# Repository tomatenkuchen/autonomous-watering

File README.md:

# autonomous-watering
esp32c6 based, solar powered, battery backuped garden water supply system

## todo
The objective of this project is to have an autonomous-as-can-be field water management system. it supports:
- [ ] multiple 24Vdc water valve connections for water distribution
- [ ] solar power supply to avoid grid wiring
- [ ] battery backup for valve power supply in case no sun is shining. watering is done best after heavy sun hours anyway
- [ ] wifi access point for watering configurations and updates
- [ ] optional conductivity sensor to measure earth humidity
- [ ] maybe maybe wifi powered wether data access to avoid watering just before the storm. GPS data relevant?
- [ ] bonus project: support for an electric fence to have sheep stay away from my salad

## Hardware

can be found in [this](./hw) folder. it's a [kicad](https://www.kicad.org) project, so no worries about licenses.
for now i plan to have an [ESP32C6] as the computing base.

## Software

is found in [this](./sw) folder. as it is an embedded project, it fits the hardware described in the [hardware folder](./hw).

## License

i intent to have the software and hardware licensed for GNU GPLv2. You will find either hardware part libraries or software libraries
licensed under different licenses (duh!), so please check the individual folders and references.

## Liabilities

this is my personal DIY project. It's supposed to be battery backed, so at least no grilling yourself on the grid issues to expected here.
nontheless, electrical danger lurks everywhere. Consider yourself to be warned! If you hurt yourself by soldering stuff, (mis-)handling batteries,
tripping over wires or get struck by lightning while setting up the system outside, blame yourself, not me.

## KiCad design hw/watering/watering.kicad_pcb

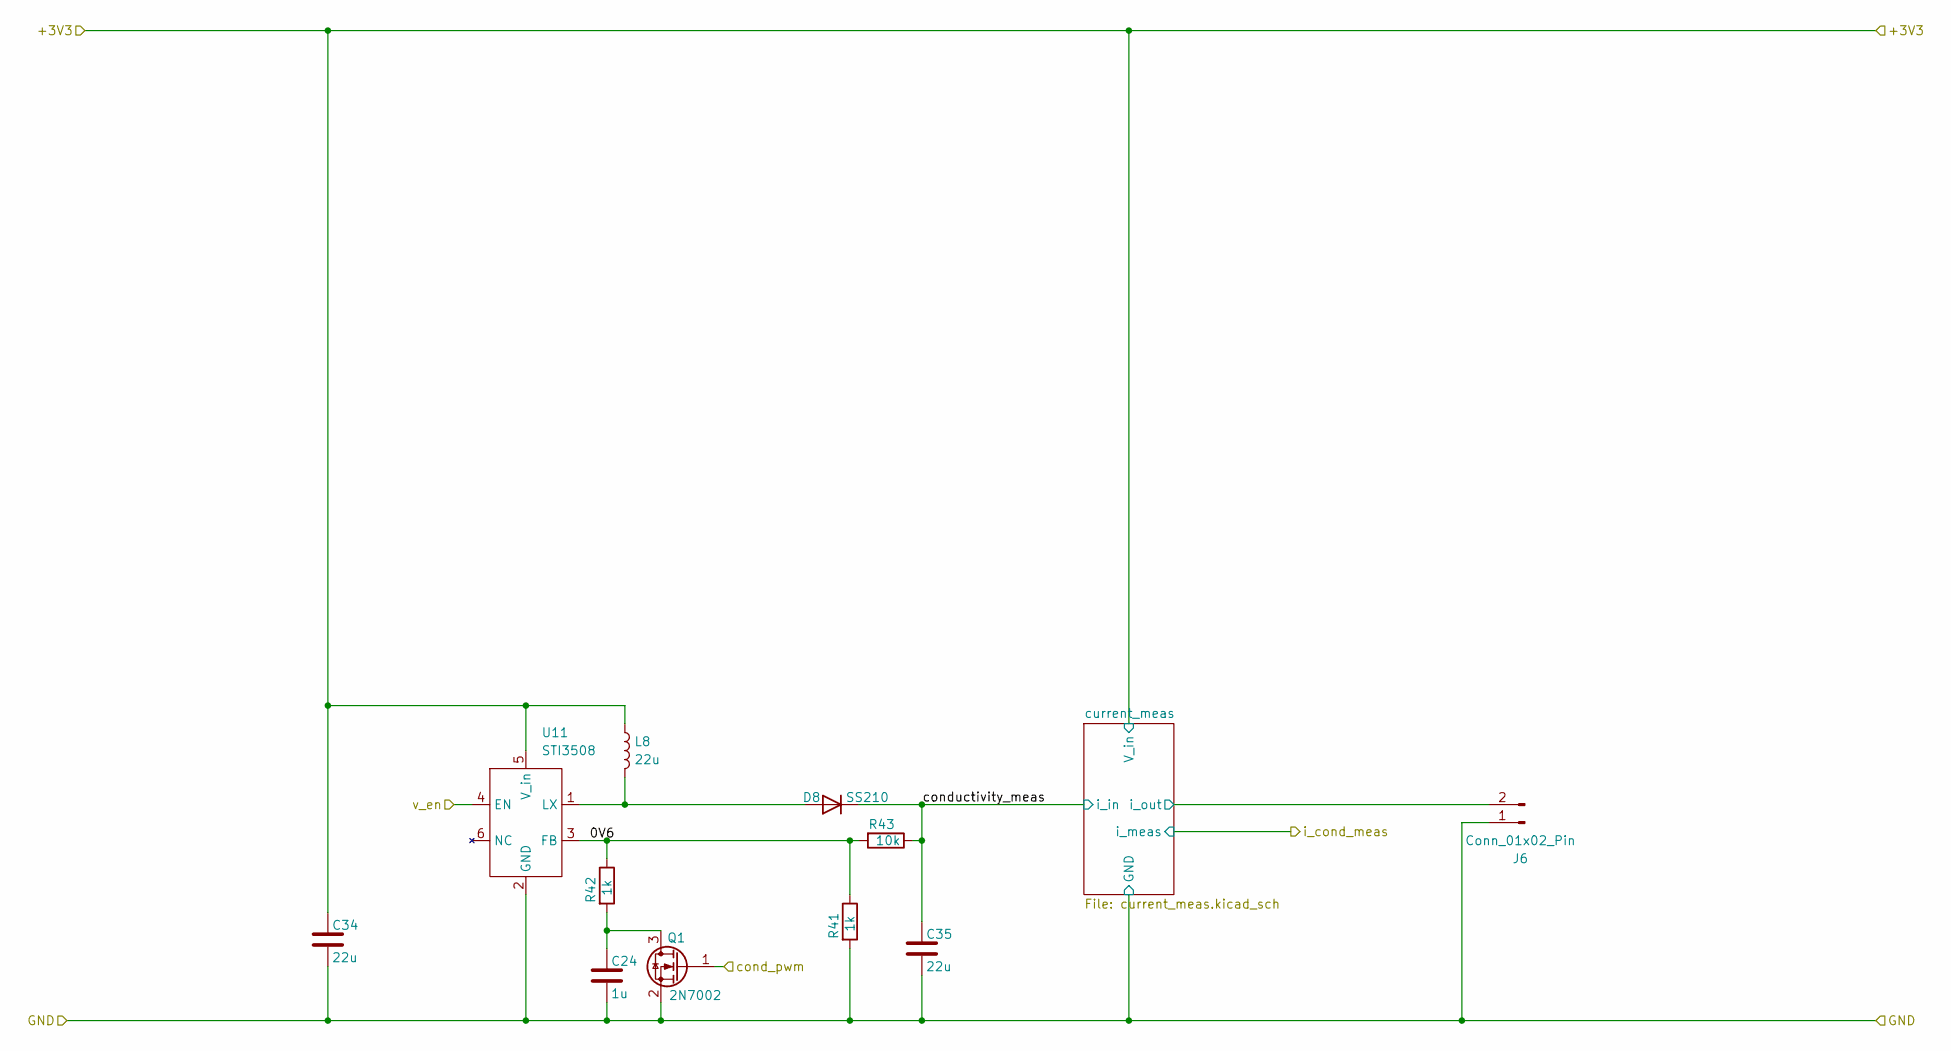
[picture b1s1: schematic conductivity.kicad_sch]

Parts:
C24: 1u; C_0603_1608Metric
C34, C35: 22u; C_1206_3216Metric
D8: SS210; D_SMA
J6: Conn_01x02_Pin; DB142R-5.08-2P-GN
L8: 22u; L_Changjiang_FTC303020D
Q1: 2N7002; SOT-23
R41, R42: 1k; R_0603_1608Metric
R43: 10k; R_0603_1608Metric
U11: STI3508; SOT-23-6

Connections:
/GND: C24.2, C34.2, C35.2, J6.1, Q1.2 (S), R41.2, U11.2 (GND); also elsewhere on the board
/V_bat: C34.1, L8.1, U11.5 (V_in); also elsewhere on the board
/conductivity/0V6: R41.1, R42.1, R43.2, U11.3 (FB)
/conductivity/cond_pwm: Q1.1 (G); also elsewhere on the board
/conductivity/conductivity_meas: C35.1, D8.1 (K), R43.1; also elsewhere on the board
/conductivity/current_meas/i_out: J6.2; also elsewhere on the board
/conductivity/v_en: U11.4 (EN); also elsewhere on the board
unnamed: D8.2 (A), L8.2, U11.1 (LX)
unnamed: C24.1, Q1.3 (D), R42.2

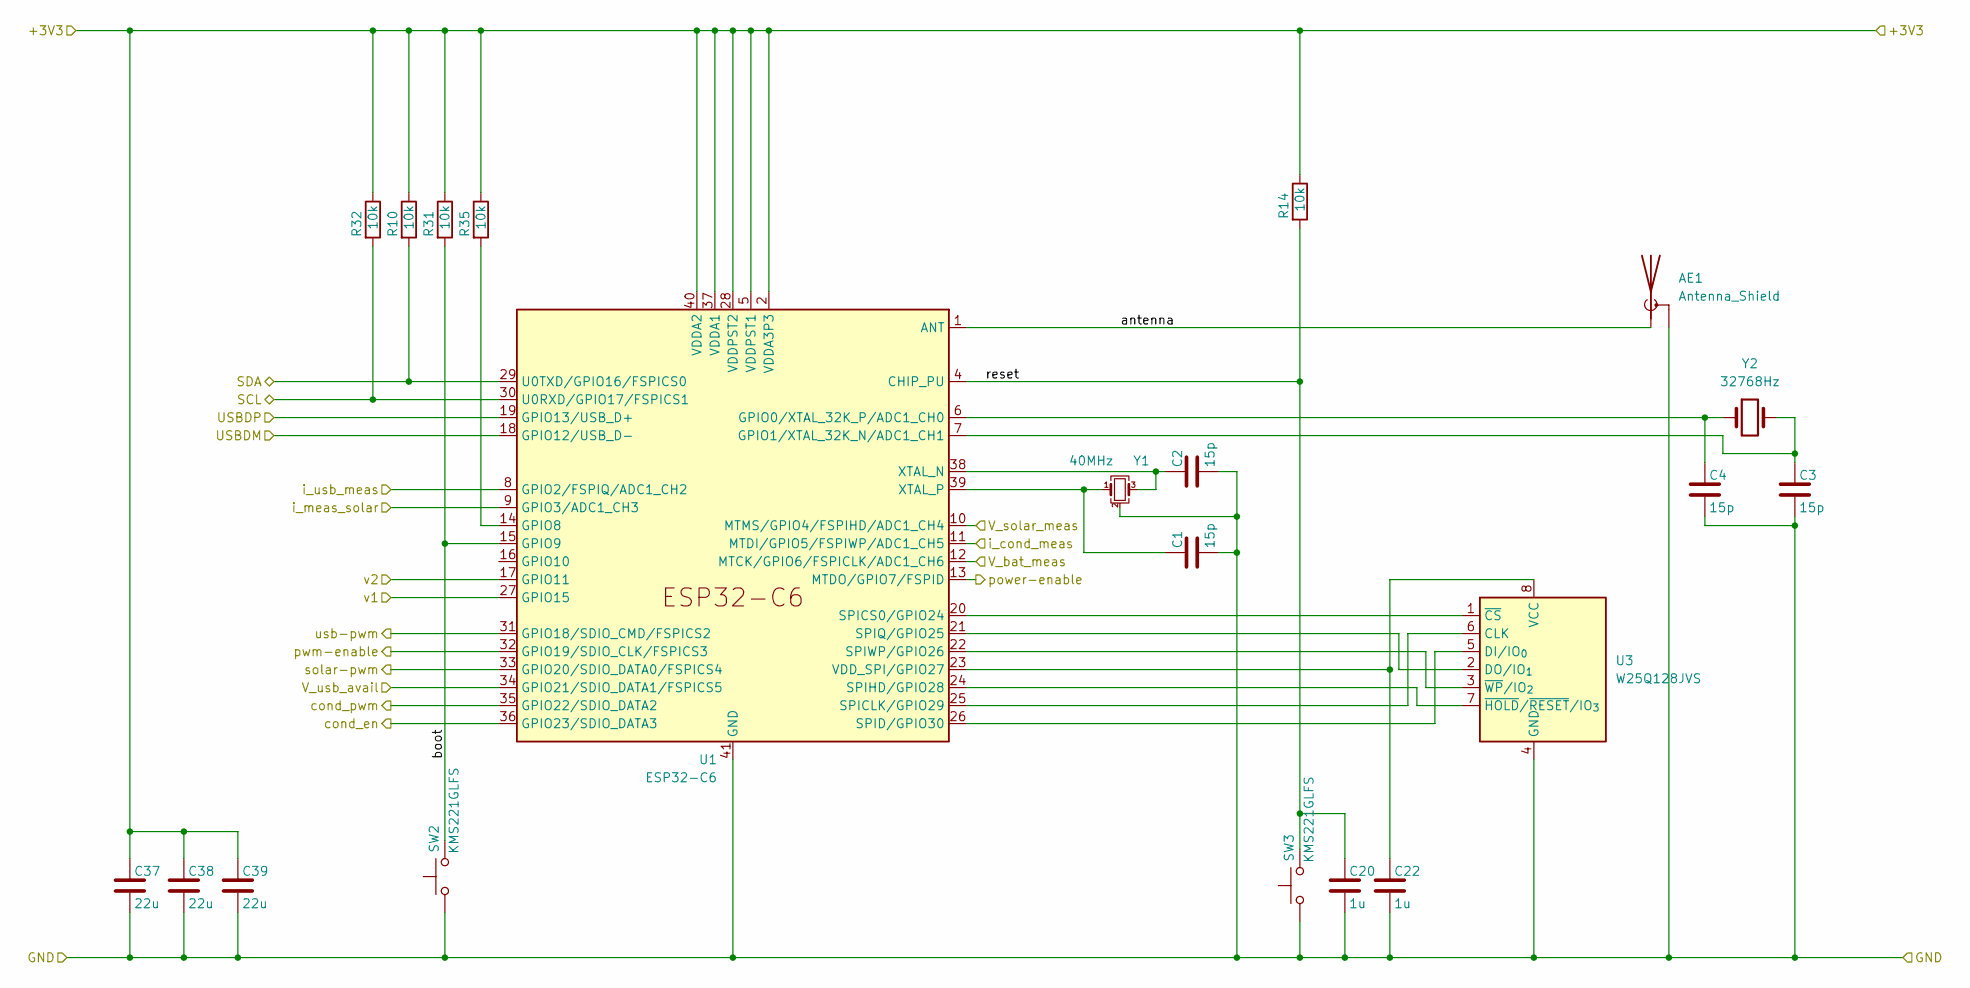
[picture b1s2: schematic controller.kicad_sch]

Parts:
AE1: Antenna_Shield; Texas_SWRA117D_2.4GHz_Left
C1, C2, C3, C4: 15p; C_0603_1608Metric
C20, C22: 1u; C_0603_1608Metric
C37, C38, C39: 22u; C_1206_3216Metric
R10, R14, R31, R32, R35: 10k; R_0603_1608Metric
SW2, SW3: KMS221GLFS; SW_SPST_TS-1088-xR020
U1: ESP32-C6; QFN-40-1EP_5x5mm_P0.4mm_EP3.6x3.6mm
U3: W25Q128JVS; SOIC-8_5.3x5.3mm_P1.27mm
Y1: 40MHz; Crystal_SMD_3225-4Pin_3.2x2.5mm
Y2: 32768Hz; Crystal_SMD_3215-2Pin_3.2x1.5mm

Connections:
/+3V3: C37.1, C38.1, C39.1, R10.1, R14.1, R31.1, R32.1, R35.1, U1.2 (VDDA3P3), U1.3 (VDDA3P3), U1.5 (VDDPST1), U1.28 (VDDPST2), U1.37 (VDDA1), U1.40 (VDDA2); also elsewhere on the board
/GND: AE1.2 (Shield), C1.2, C2.2, C3.2, C4.2, C20.2, C22.2, C37.2, C38.2, C39.2, SW2.1, SW3.1, U1.41 (GND), U3.4 (GND), Y1.2 (G), Y1.4 (G); also elsewhere on the board
/conductivity/cond_pwm: U1.35 (GPIO22/SDIO_DATA2); also elsewhere on the board
/conductivity/i_cond_meas: U1.11 (MTDI/GPIO5/FSPIWP/ADC1_CH5); also elsewhere on the board
/conductivity/v_en: U1.36 (GPIO23/SDIO_DATA3); also elsewhere on the board
/controller/SCL: R32.2, U1.30 (U0RXD/GPIO17/FSPICS1)
/controller/SDA: R10.2, U1.29 (U0TXD/GPIO16/FSPICS0)
/controller/USBDM: U1.18 (GPIO12/USB_D-); also elsewhere on the board
/controller/USBDP: U1.19 (GPIO13/USB_D+); also elsewhere on the board
/controller/V_bat_meas: U1.12 (MTCK/GPIO6/FSPICLK/ADC1_CH6); also elsewhere on the board
/controller/V_solar_meas: U1.10 (MTMS/GPIO4/FSPIHD/ADC1_CH4); also elsewhere on the board
/controller/V_usb_avail: U1.34 (GPIO21/SDIO_DATA1/FSPICS5); also elsewhere on the board
/controller/antenna: AE1.1 (A), U1.1 (ANT)
/controller/boot: R31.2, SW2.2, U1.15 (GPIO9)
/controller/i_meas_solar: U1.9 (GPIO3/ADC1_CH3); also elsewhere on the board
/controller/i_usb_meas: U1.8 (GPIO2/FSPIQ/ADC1_CH2); also elsewhere on the board
/controller/power-enable: U1.13 (MTDO/GPIO7/FSPID)
/controller/pwm-enable: U1.32 (GPIO19/SDIO_CLK/FSPICS3); also elsewhere on the board
/controller/reset: C20.1, R14.2, SW3.2, U1.4 (CHIP_PU)
/controller/solar-pwm: U1.33 (GPIO20/SDIO_DATA0/FSPICS4); also elsewhere on the board
/controller/usb-pwm: U1.31 (GPIO18/SDIO_CMD/FSPICS2); also elsewhere on the board
/controller/v1: U1.27 (GPIO15); also elsewhere on the board
/controller/v2: U1.17 (GPIO11); also elsewhere on the board
unnamed: C4.1, U1.6 (GPIO0/XTAL_32K_P/ADC1_CH0), Y2.1
unnamed: C3.1, U1.7 (GPIO1/XTAL_32K_N/ADC1_CH1), Y2.2
unnamed: R35.2, U1.14 (GPIO8)
unnamed: U1.25 (SPICLK/GPIO29), U3.6 (CLK)
unnamed: U1.20 (SPICS0/GPIO24), U3.1 (~CS)
unnamed: U1.26 (SPID/GPIO30), U3.5 (DI/IO_{0})
unnamed: U1.24 (SPIHD/GPIO28), U3.7 (~HOLD/~RESET/IO_{3})
unnamed: U1.21 (SPIQ/GPIO25), U3.2 (DO/IO_{1})
unnamed: U1.22 (SPIWP/GPIO26), U3.3 (~WP/IO_{2})
unnamed: C22.1, U1.23 (VDD_SPI/GPIO27), U3.8 (VCC)
unnamed: C2.1, U1.38 (XTAL_N), Y1.3
unnamed: C1.1, U1.39 (XTAL_P), Y1.1

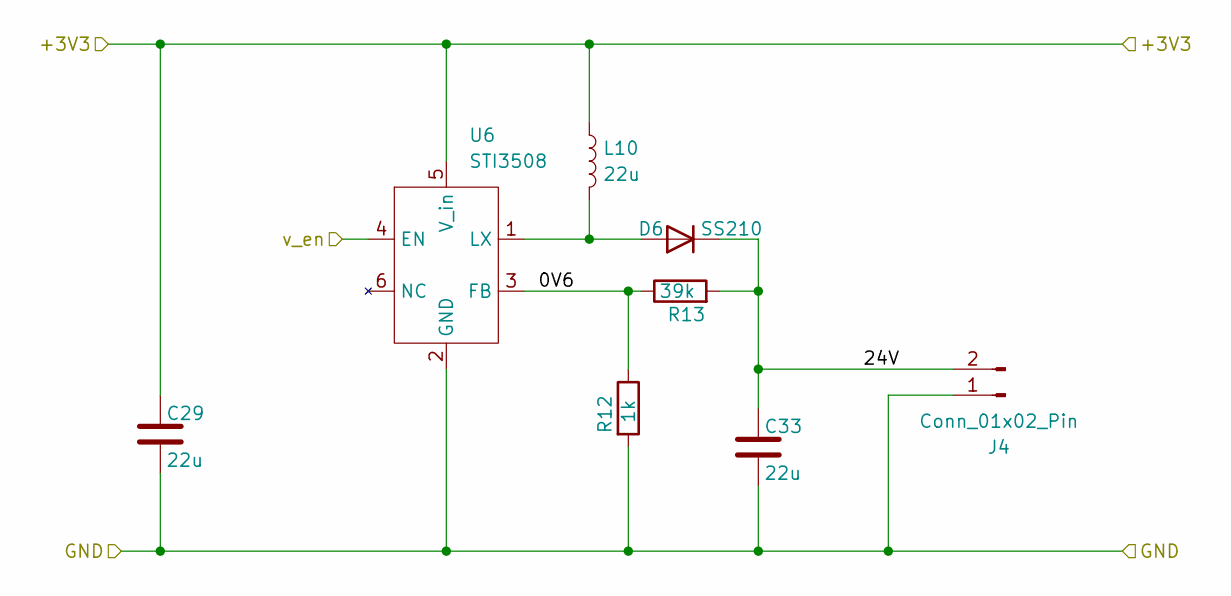
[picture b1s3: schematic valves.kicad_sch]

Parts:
C29, C33: 22u; C_1206_3216Metric
D6: SS210; D_SMA
J4: Conn_01x02_Pin; DB142R-5.08-2P-GN
L10: 22u; L_Changjiang_FTC303020D
R12: 1k; R_0603_1608Metric
R13: 39k; R_0603_1608Metric
U6: STI3508; SOT-23-6

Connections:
/GND: C29.2, C33.2, J4.1, R12.2, U6.2 (GND); also elsewhere on the board
/V_bat: C29.1, L10.1, U6.5 (V_in); also elsewhere on the board
/controller/v2: U6.4 (EN); also elsewhere on the board
/valves2/0V6: R12.1, R13.1, U6.3 (FB)
/valves2/24V: C33.1, D6.1 (K), J4.2, R13.2
unnamed: D6.2 (A), L10.2, U6.1 (LX)

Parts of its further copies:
C28, C30: 22u; C_1206_3216Metric
D7: SS210; D_SMA
J3: Conn_01x02_Pin; DB142R-5.08-2P-GN
L11: 22u; L_Changjiang_FTC303020D
R5: 1k; R_0603_1608Metric
R6: 39k; R_0603_1608Metric
U4: STI3508; SOT-23-6

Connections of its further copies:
/GND: C28.2, C30.2, J3.1, R5.2, U4.2 (GND); also elsewhere on the board
/V_bat: C28.1, L11.1, U4.5 (V_in); also elsewhere on the board
/controller/v1: U4.4 (EN); also elsewhere on the board
/valves1/0V6: R5.1, R6.1, U4.3 (FB)
/valves1/24V: C30.1, D7.1 (K), J3.2, R6.2
unnamed: D7.2 (A), L11.2, U4.1 (LX)

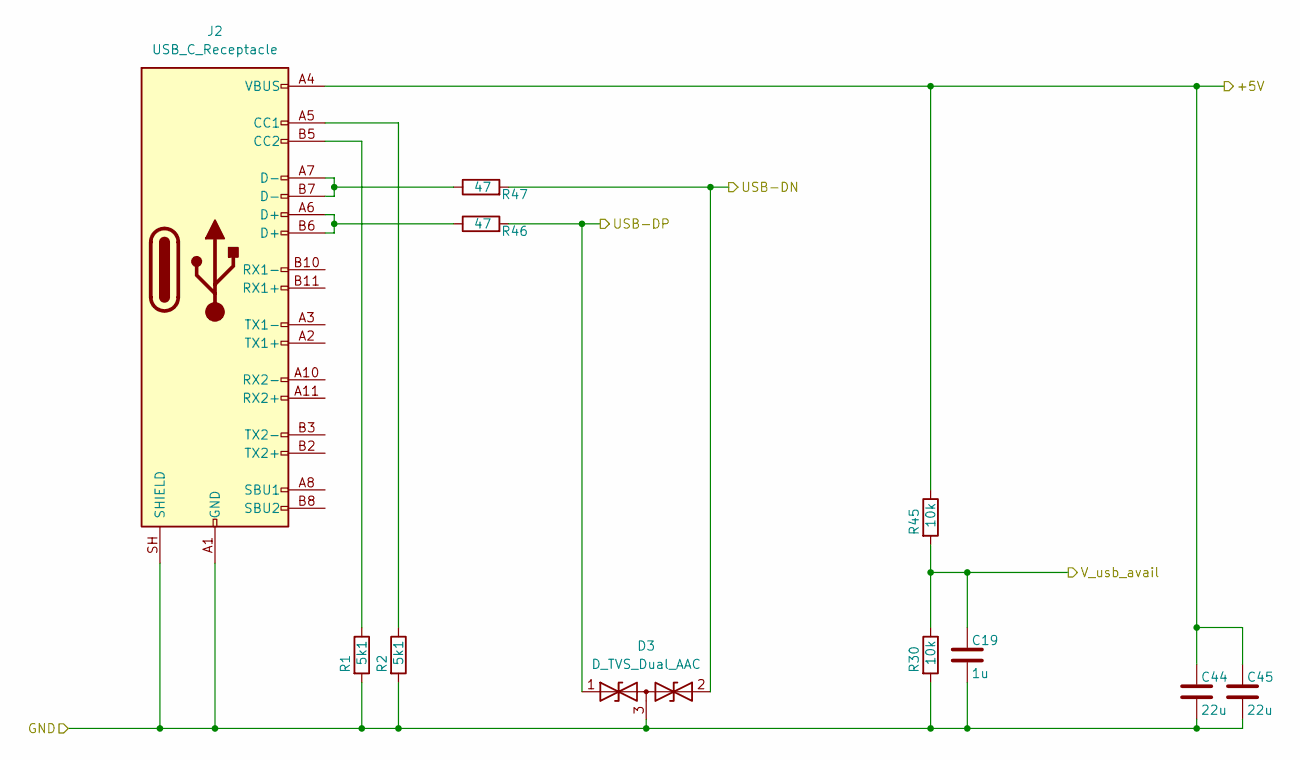
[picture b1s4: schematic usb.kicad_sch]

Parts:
C19: 1u; C_0603_1608Metric
C44, C45: 22u; C_1206_3216Metric
D3: D_TVS_Dual_AAC; TSOT-23
J2: USB_C_Receptacle; USB_C_Receptacle_GCT_USB4105-xx-A_16P_TopMnt_Horizontal
R1, R2: 5k1; R_0603_1608Metric
R30, R45: 10k; R_0603_1608Metric
R46, R47: 47; R_0603_1608Metric

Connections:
/+5V: C44.1, C45.1, J2.A4 (VBUS), J2.A9 (VBUS), J2.B4 (VBUS), J2.B9 (VBUS), R45.1; also elsewhere on the board
/GND: C19.2, C44.2, C45.2, D3.3 (common), J2.A1 (GND), J2.A12 (GND), J2.B1 (GND), J2.B12 (GND), J2.SH (SHIELD), R1.2, R2.2, R30.2; also elsewhere on the board
/controller/USBDM: D3.2 (A2), R47.2; also elsewhere on the board
/controller/USBDP: D3.1 (A1), R46.2; also elsewhere on the board
/controller/V_usb_avail: C19.1, R30.1, R45.2; also elsewhere on the board
unnamed: J2.A5 (CC1), R2.1
unnamed: J2.B5 (CC2), R1.1
unnamed: J2.A6 (D+), J2.B6 (D+), R46.1
unnamed: J2.A7 (D-), J2.B7 (D-), R47.1

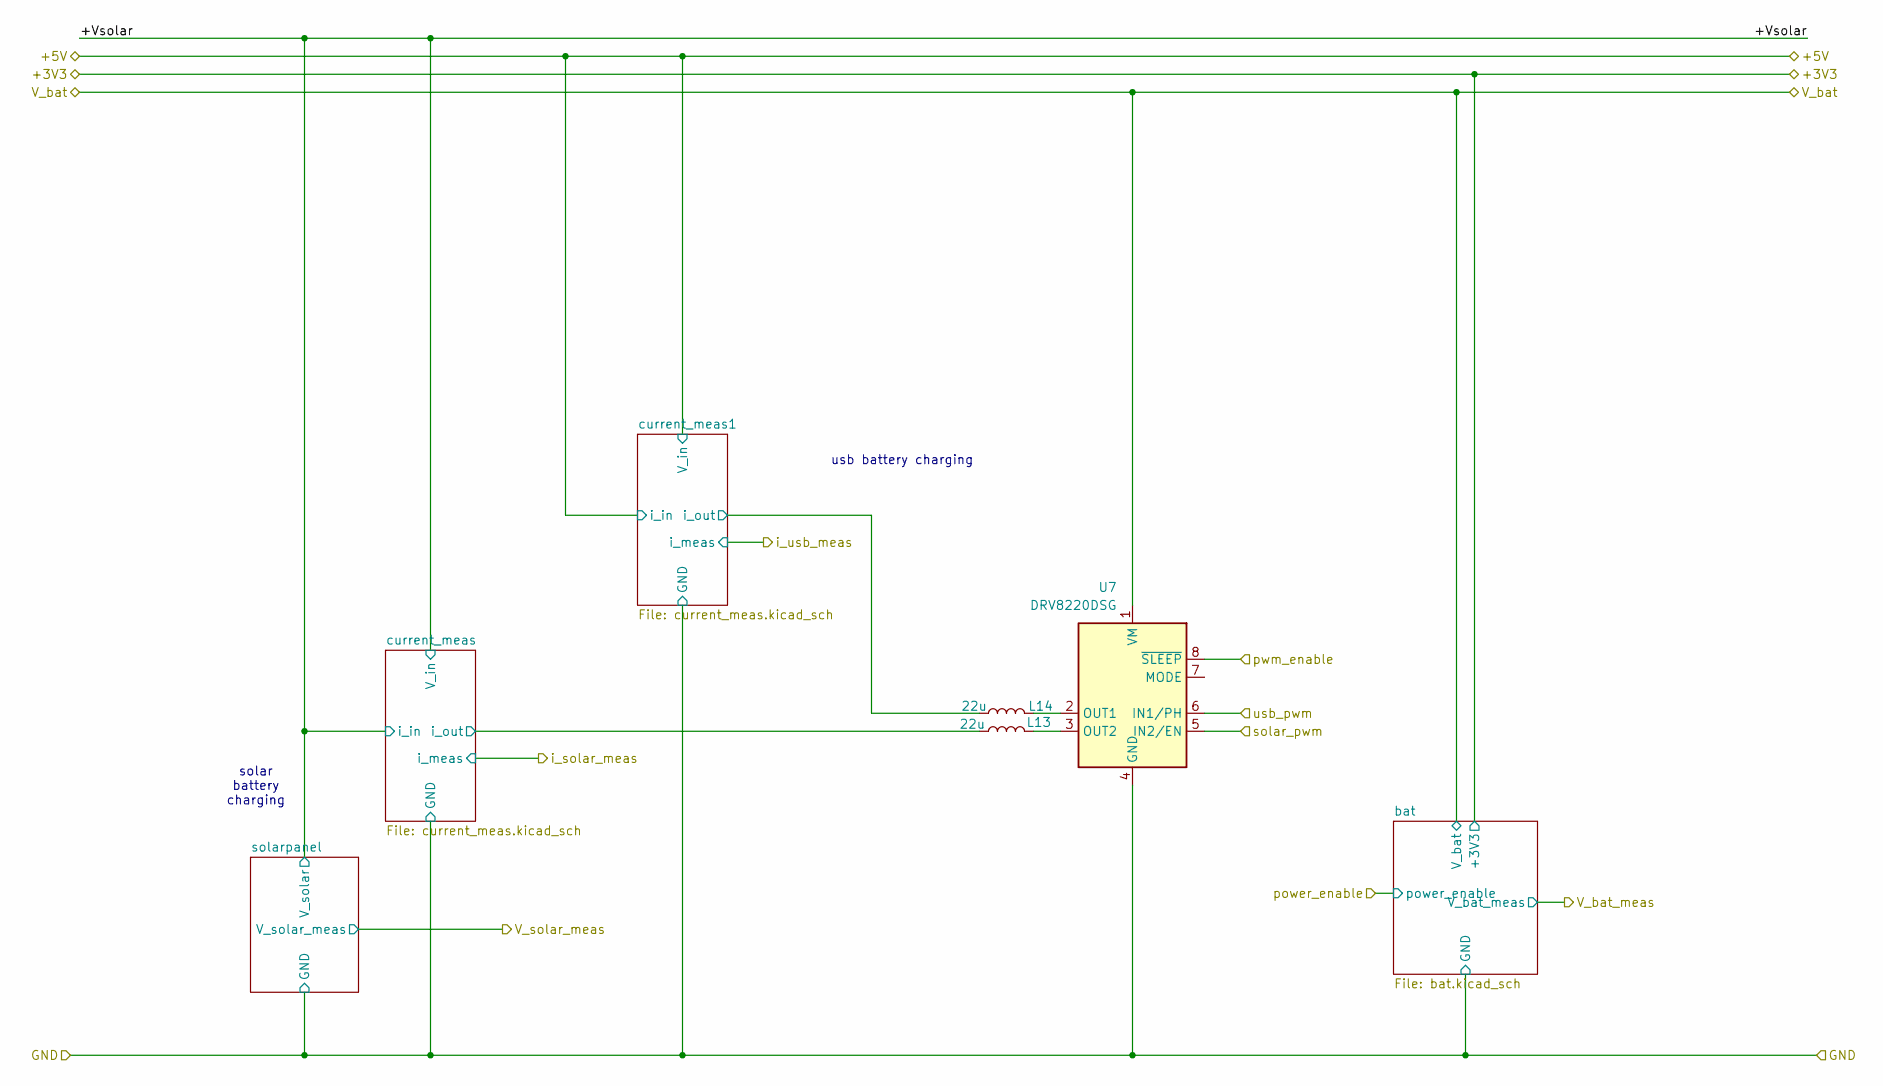
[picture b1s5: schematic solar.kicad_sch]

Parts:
L13, L14: 22u; L_Changjiang_FTC303020D
U7: DRV8220DSG; Texas_DSG0008A_WSON-8-1EP_2x2mm_P0.5mm_EP0.9x1.6mm

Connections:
/GND: U7.4 (GND), U7.9 (GND); also elsewhere on the board
/V_bat: U7.1 (VM); also elsewhere on the board
/controller/pwm-enable: U7.8 (~SLEEP); also elsewhere on the board
/controller/solar-pwm: U7.5 (IN2/EN); also elsewhere on the board
/controller/usb-pwm: U7.6 (IN1/PH); also elsewhere on the board
/solar/current_meas1/i_out: L14.2; also elsewhere on the board
/solar/current_meas/i_out: L13.2; also elsewhere on the board
unnamed: L14.1, U7.2 (OUT1)
unnamed: L13.1, U7.3 (OUT2)

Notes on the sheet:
usb battery charging
solar battery charging

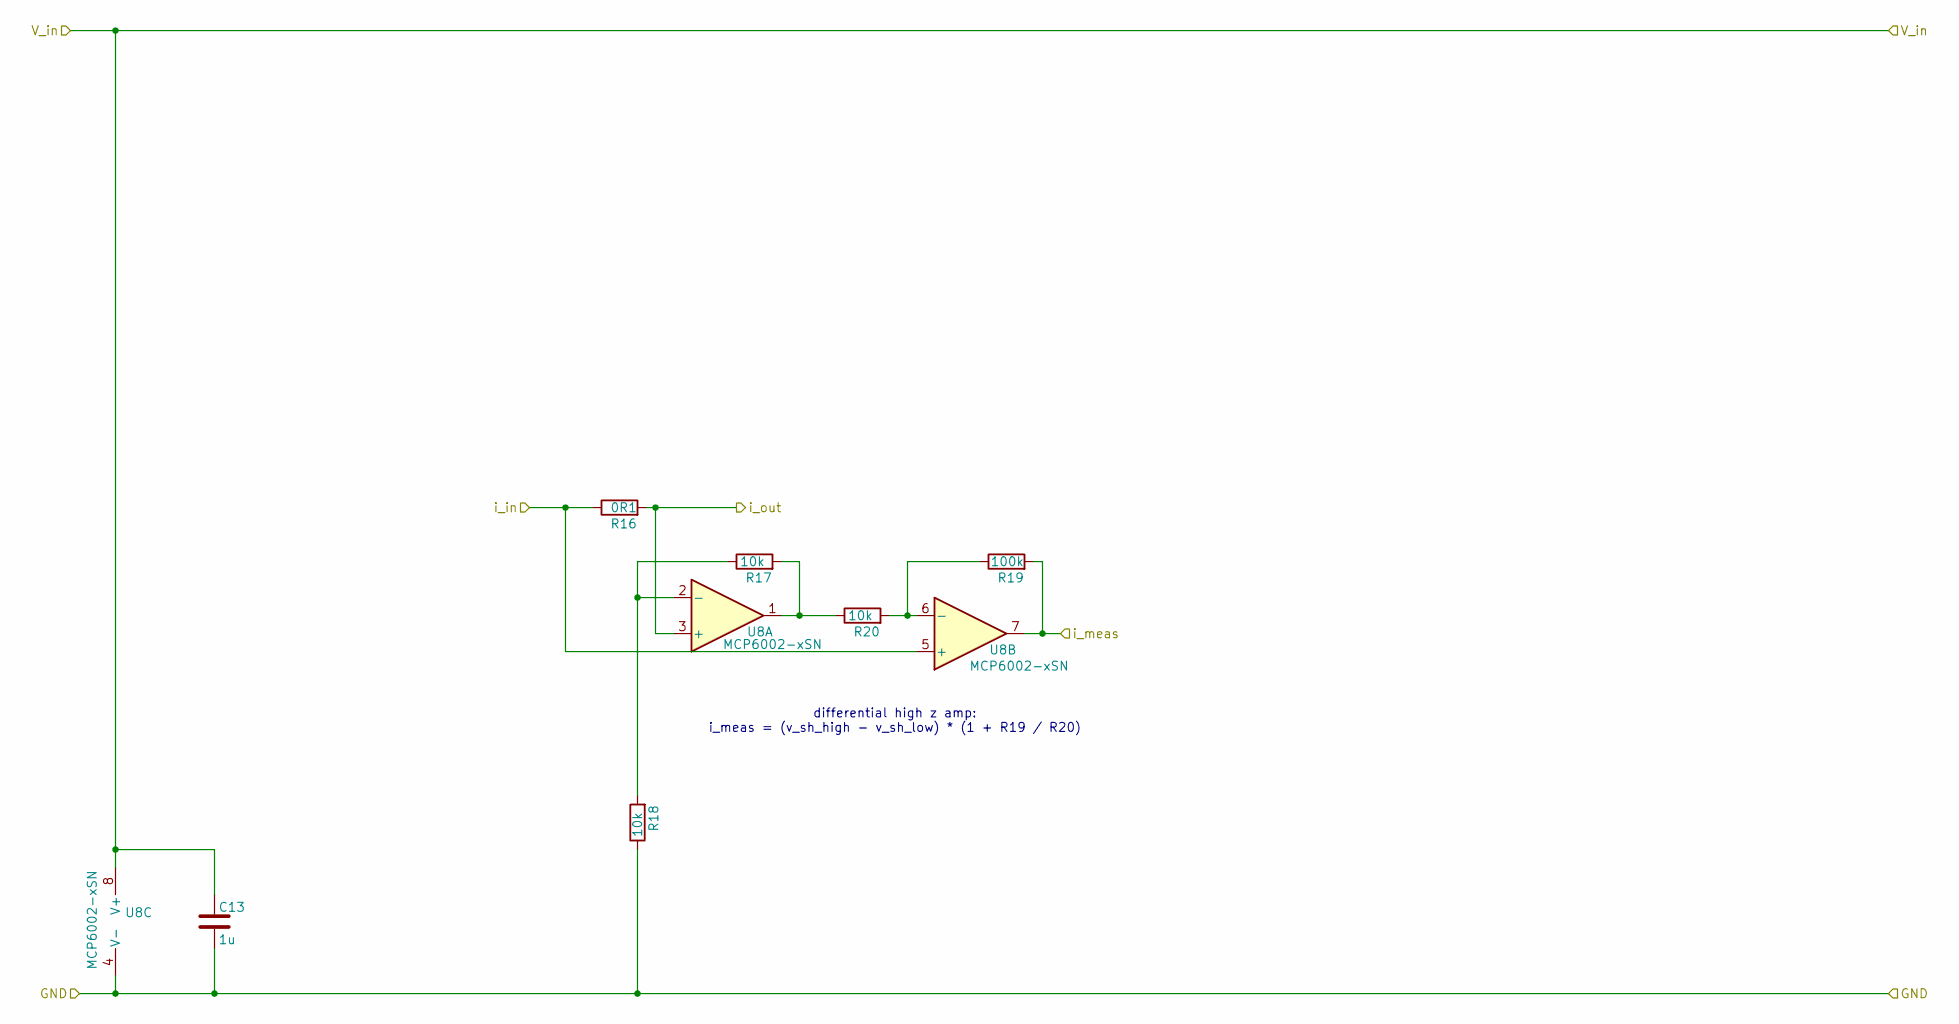
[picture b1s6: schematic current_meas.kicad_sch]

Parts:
C13: 1u; C_0603_1608Metric
R16: 0R1; R_1206_3216Metric
R17, R18, R20: 10k; R_0603_1608Metric
R19: 100k; R_0603_1608Metric
U8: MCP6002-xSN; SOIC-8_3.9x4.9mm_P1.27mm

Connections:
/GND: C13.2, R18.1, U8.4 (V-); also elsewhere on the board
/controller/i_meas_solar: R19.2, U8.7; also elsewhere on the board
/solar/+Vsolar: C13.1, R16.1, U8.5 (+), U8.8 (V+); also elsewhere on the board
/solar/current_meas/i_out: R16.2, U8.3 (+); also elsewhere on the board
unnamed: R17.2, R20.1, U8.1
unnamed: R17.1, R18.2, U8.2 (-)
unnamed: R19.1, R20.2, U8.6 (-)

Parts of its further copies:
C14, C21: 1u; C_0603_1608Metric
R22, R36: 0R1; R_1206_3216Metric
R23, R24, R25, R37, R38, R39: 10k; R_0603_1608Metric
R26, R40: 100k; R_0603_1608Metric
U9, U10: MCP6002-xSN; SOIC-8_3.9x4.9mm_P1.27mm

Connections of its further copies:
/+5V: C14.1, R22.1, U9.5 (+), U9.8 (V+); also elsewhere on the board
/GND: C14.2, C21.2, R23.1, R37.1, U9.4 (V-), U10.4 (V-); also elsewhere on the board
/V_bat: C21.1, U10.8 (V+); also elsewhere on the board
/conductivity/conductivity_meas: R36.1, U10.5 (+); also elsewhere on the board
/conductivity/current_meas/i_out: R36.2, U10.3 (+); also elsewhere on the board
/conductivity/i_cond_meas: R40.2, U10.7; also elsewhere on the board
/controller/i_usb_meas: R26.2, U9.7; also elsewhere on the board
/solar/current_meas1/i_out: R22.2, U9.3 (+); also elsewhere on the board
unnamed: R24.2, R25.1, U9.1
unnamed: R38.2, R39.1, U10.1
unnamed: R23.2, R24.1, U9.2 (-)
unnamed: R25.2, R26.1, U9.6 (-)
unnamed: R37.2, R38.1, U10.2 (-)
unnamed: R39.2, R40.1, U10.6 (-)

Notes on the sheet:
differential high z amp: i_meas = (v_sh_high - v_sh_low) * (1 + R19 / R20)

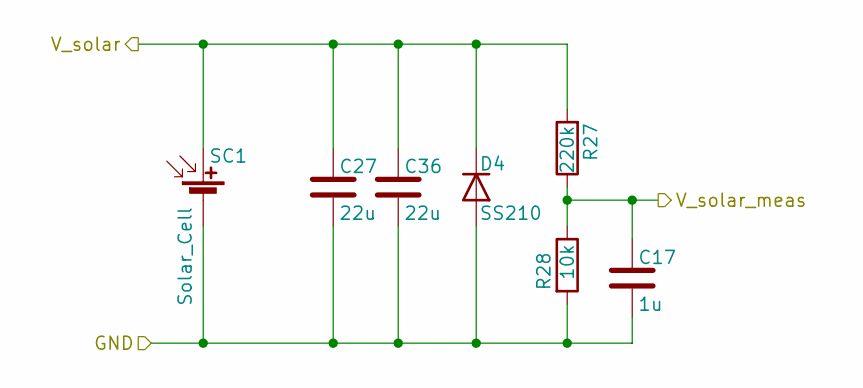
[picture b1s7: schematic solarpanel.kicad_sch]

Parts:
C17: 1u; C_0603_1608Metric
C27, C36: 22u; C_1206_3216Metric
D4: SS210; D_SMA
R27: 220k; R_0603_1608Metric
R28: 10k; R_0603_1608Metric
SC1: Solar_Cell; DB142R-5.08-2P-GN

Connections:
/GND: C17.2, C27.2, C36.2, D4.2 (A), R28.2, SC1.2 (-); also elsewhere on the board
/controller/V_solar_meas: C17.1, R27.1, R28.1; also elsewhere on the board
/solar/+Vsolar: C27.1, C36.1, D4.1 (K), R27.2, SC1.1 (+); also elsewhere on the board

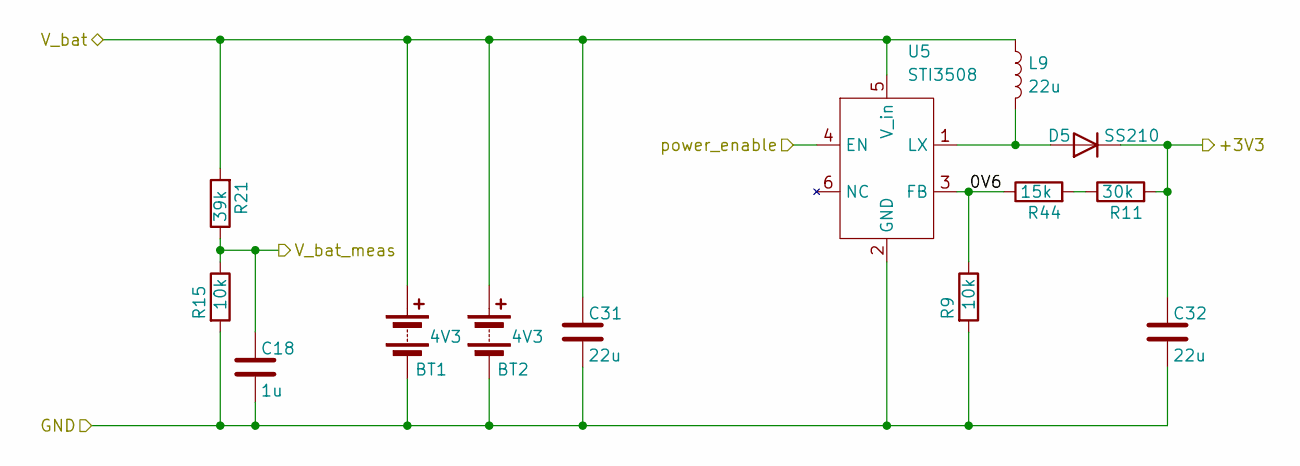
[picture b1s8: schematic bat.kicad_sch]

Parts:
BT1, BT2: 4V3; BH-18650-B1BA002
C18: 1u; C_0603_1608Metric
C31, C32: 22u; C_1206_3216Metric
D5: SS210; D_SMA
L9: 22u; L_Changjiang_FTC303020D
R9, R15: 10k; R_0603_1608Metric
R11: 30k; R_0603_1608Metric
R21: 39k; R_0603_1608Metric
R44: 15k; R_0603_1608Metric
U5: STI3508; SOT-23-6

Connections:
/+3V3: C32.1, D5.1 (K), R11.2; also elsewhere on the board
/GND: BT1.2 (-), BT2.2 (-), C18.2, C31.2, C32.2, R9.2, R15.2, U5.2 (GND); also elsewhere on the board
/V_bat: BT1.1 (+), BT2.1 (+), C31.1, L9.1, R21.2, U5.5 (V_in); also elsewhere on the board
/controller/V_bat_meas: C18.1, R15.1, R21.1; also elsewhere on the board
/solar/bat/0V6: R9.1, R44.1, U5.3 (FB)
/solar/power_enable: U5.4 (EN)
unnamed: D5.2 (A), L9.2, U5.1 (LX)
unnamed: R11.1, R44.2

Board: 2 copper layers, 103 parts (2 on the bottom side), 68 nets, no tracks yet.

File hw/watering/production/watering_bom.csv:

Designator,Footprint,Quantity,Value,LCSC Part #
AE1,Texas_SWRA117D_2.4GHz_Left,1,Antenna_Shield,
"BT1, BT2",BH-18650-B1BA002,2,4V3,C2988620
"C1, C2",603,2,15p,C1644
"C13, C14, C15, C16, C17, C18, C19, C20, C21, C24",603,10,1u,C15849
"C26, C27, C28, C29, C30, C31, C32, C33, C34, C35, C36",1206,11,22u,C12891
"C5, C6, C7",603,3,100n,C14663
D3,TSOT-23,1,D_TVS_Dual_AAC,C32677
"D4, D5, D6, D7, D8",D_SMA,5,SS210,C14996
J2,USB_C_Receptacle_GCT_USB4105-xx-A_16P_TopMnt_Horizontal,1,USB_C_Receptacle,C2927038
"J3, J4, J6",DB142R-5.08-2P-GN,3,Conn_01x02_Pin,C2898709
"L10, L11, L13, L14, L8, L9",L_Changjiang_FTC303020D,6,22u,C18724424
Q1,SOT-23,1,2N7002,C8545
"R1, R2",603,2,5k1,C23186
"R10, R14, R15, R17, R18, R20, R23, R24, R25, R28, R30, R31, R32, R35, R37, R38, R39, R43, R9",603,19,10k,C25804
"R11, R29",603,2,47k,C25819
"R12, R41, R42, R5",603,4,1k,C21190
"R13, R21, R6",603,3,39k,C23153
"R16, R22, R36",1206,3,0R1,C25334
"R19, R26, R40",603,3,100k,C25803
R27,603,1,220k,C22961
"R33, R34",603,2,47,C23182
SC1,DB142R-5.08-2P-GN,1,Solar_Cell,C2898709
"SW2, SW3",SW_SPST_TS-1088-xR020,2,KMS221GLFS,C720477
U1,QFN-40-1EP_5x5mm_P0.4mm_EP3.6x3.6mm,1,ESP32-C6,C5364646
"U10, U8, U9",SOIC-8_3.9x4.9mm_P1.27mm,3,MCP6002-xSN,C7377
"U11, U4, U5, U6",SOT-23-6,4,STI3508,C708881
U2,WSON-8-1EP_2x2mm_P0.5mm_EP0.9x1.6mm,1,DRV8220DSG,C3681269
U3,SOIC-8_5.3x5.3mm_P1.27mm,1,W25Q128JVS,C97521
U7,WLCSP-4_0.64x0.64mm_Layout2x2_P0.35mm,1,NCP163AFCT330T2G,C603648
Y1,Crystal_SMD_3225-4Pin_3.2x2.5mm,1,40MHz,C9010
Y2,Crystal_SMD_3215-2Pin_3.2x1.5mm,1,32768Hz,C32346

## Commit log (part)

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2026-05-15 initial readme
2026-05-15 initial software setup with conan support
2026-05-15 some progress toward usability
2026-05-16 adc bsp package
2026-05-16 progress
2026-05-17 changed chip to esp32c6
2026-05-17 - changed clangformat for constructor initializations to be always newlined - adaptation of adc class to esp32c6 - adaptation of channel definition to xiao esp32c6 module
2026-05-27 added esp32c6
2026-05-27 added battery management chip
2026-05-30 added supply chip for battery and solar
2026-06-04 updated power
2026-06-04 hardware progres
2026-06-06 some progress on energy harvesting
2026-06-07 connections completet. started placing and routing
2026-06-08 some more placing
2026-06-10 routing done
2026-06-10 - updated parts numbers - created jlc outputs
2026-06-11 chores
2026-06-13 updated switches
2026-06-13 updated bom
2026-06-15 updated inductors
2026-06-24 more usb compliance
2026-06-24 - updated bom - updated dorabo connector footprint - added some stitching vias
2026-06-24 - added naming to adc inputs - added pwm class
2026-06-24 some more pwm and valves
2026-06-24 compiles
2026-06-24 resolved invalid speed settings
